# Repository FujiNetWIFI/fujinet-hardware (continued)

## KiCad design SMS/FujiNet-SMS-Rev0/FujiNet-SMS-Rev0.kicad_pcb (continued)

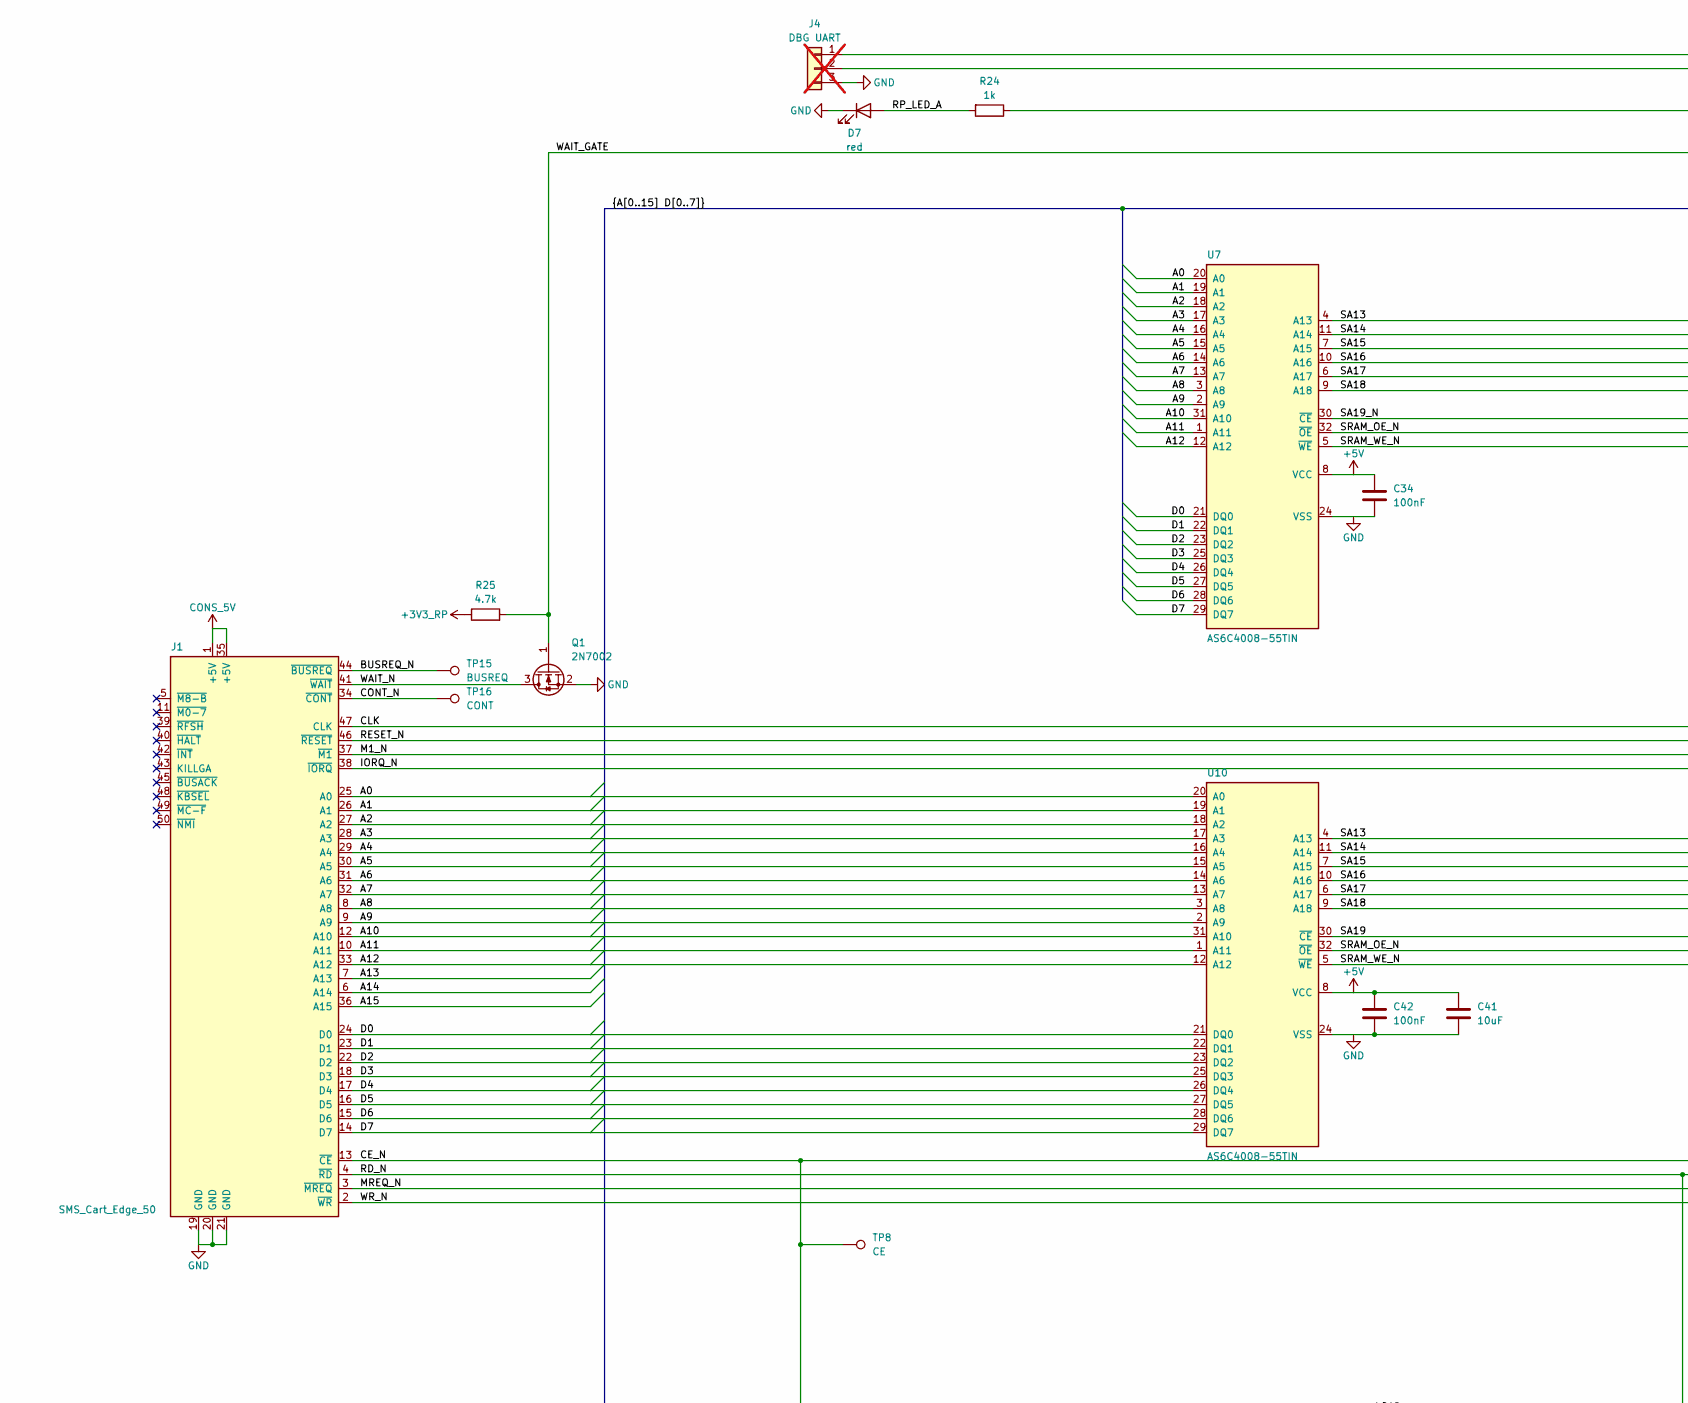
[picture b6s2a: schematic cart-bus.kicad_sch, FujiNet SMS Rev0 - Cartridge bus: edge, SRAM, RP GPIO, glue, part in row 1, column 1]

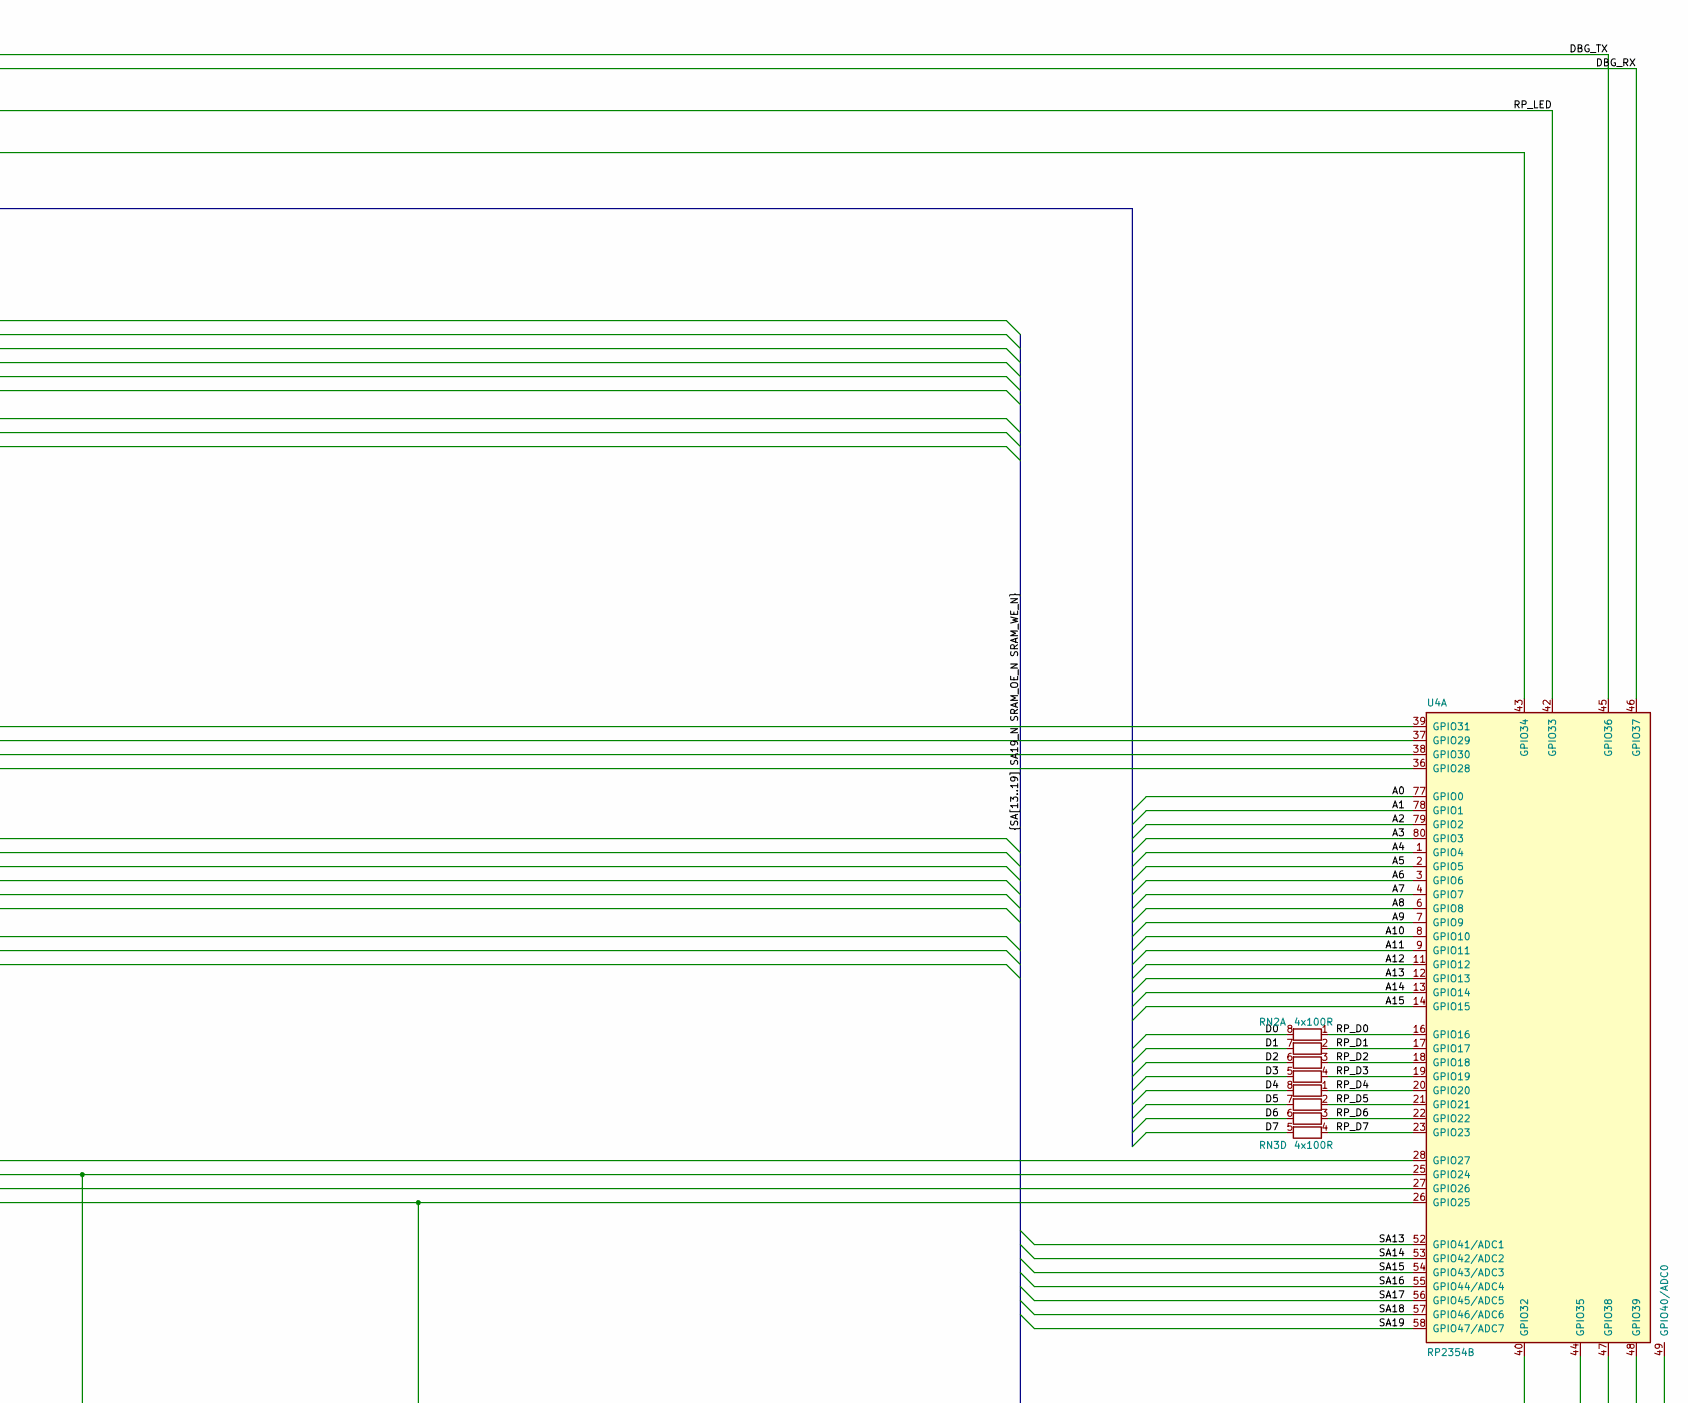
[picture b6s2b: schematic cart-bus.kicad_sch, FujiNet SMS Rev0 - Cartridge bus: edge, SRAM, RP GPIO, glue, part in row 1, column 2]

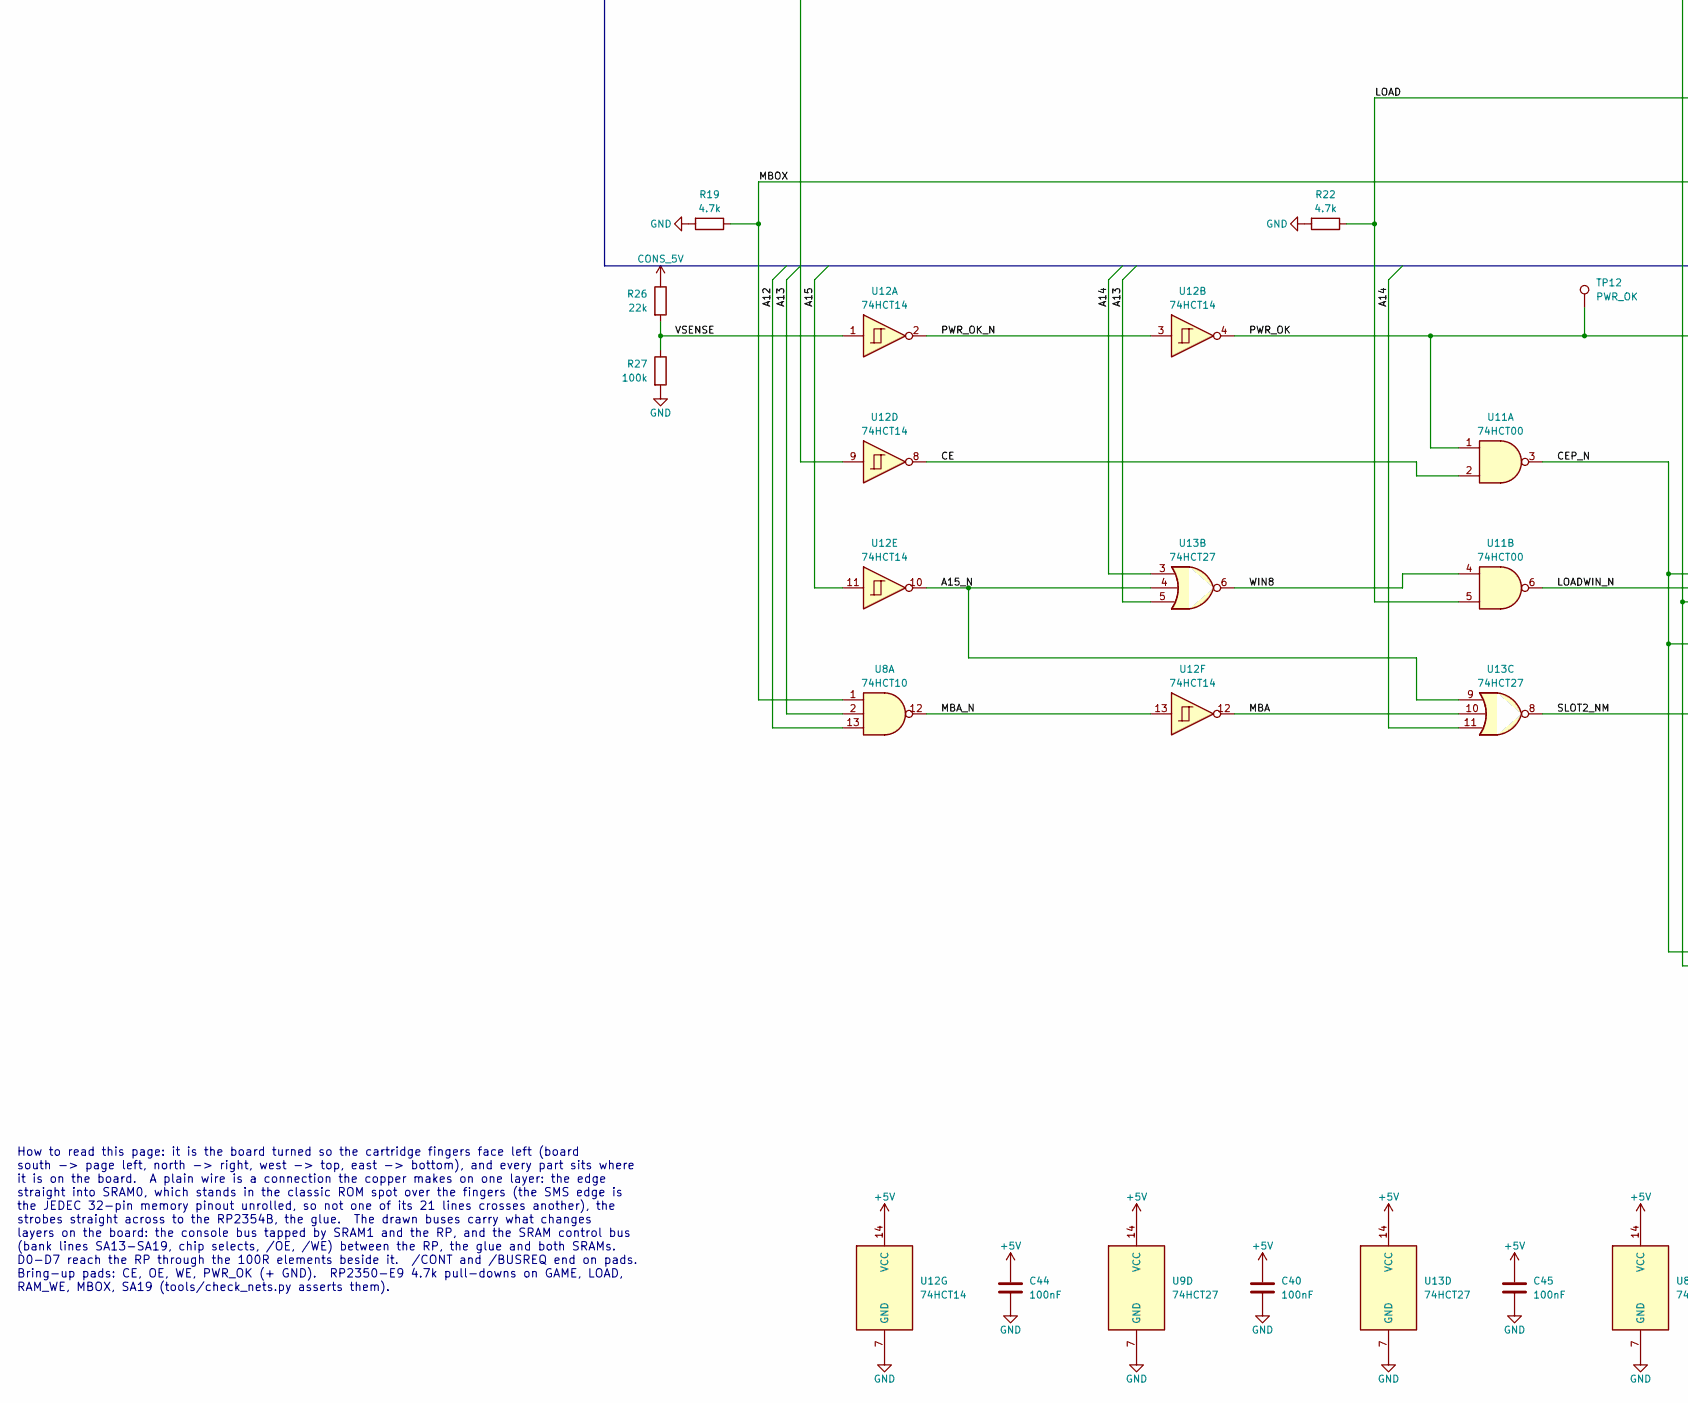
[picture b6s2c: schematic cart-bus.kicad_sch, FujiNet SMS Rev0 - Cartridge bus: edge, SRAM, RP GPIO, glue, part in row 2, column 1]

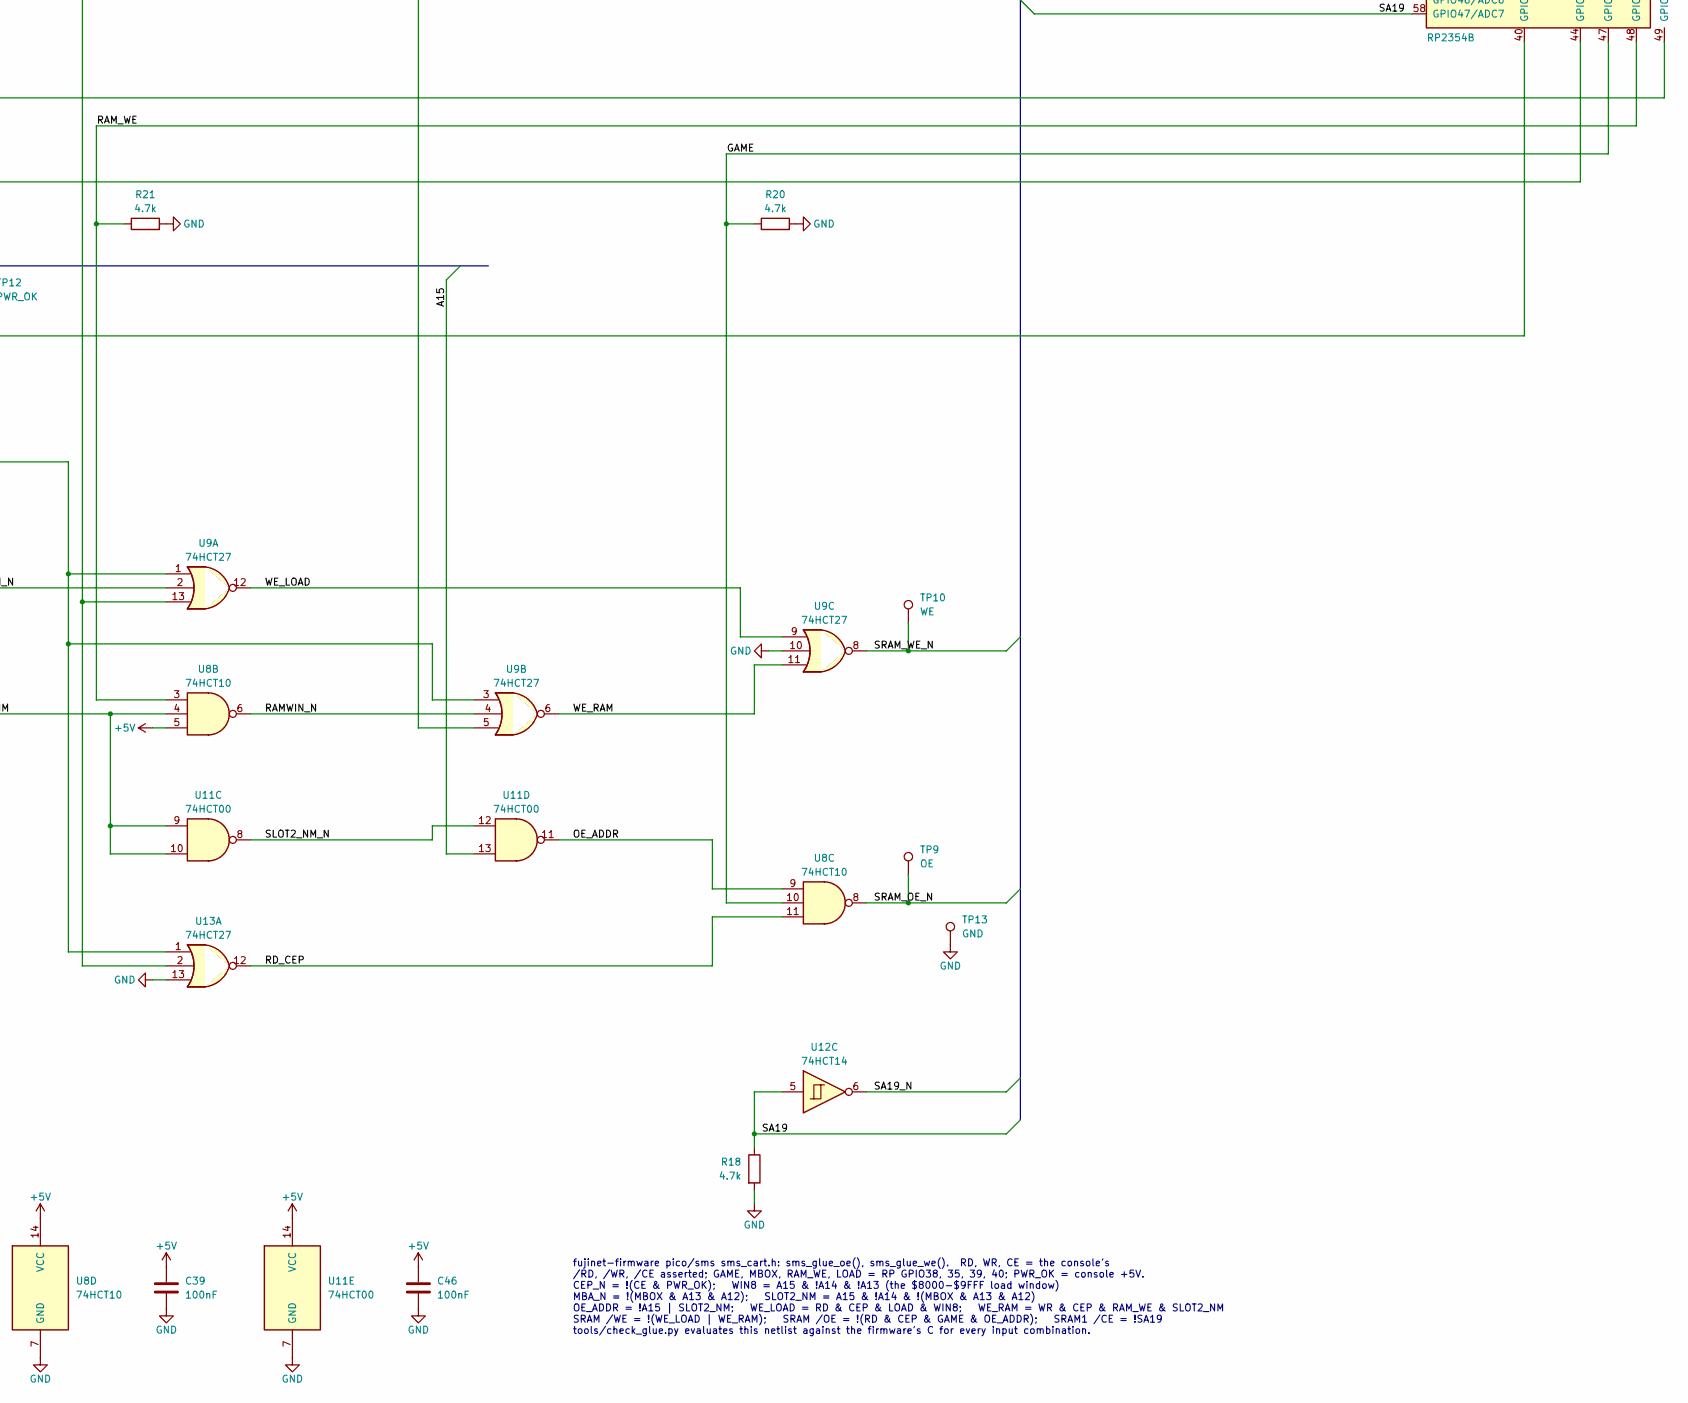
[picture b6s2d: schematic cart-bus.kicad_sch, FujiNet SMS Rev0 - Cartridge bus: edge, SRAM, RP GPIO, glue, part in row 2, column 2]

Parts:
C34, C39, C40, C42, C44, C45, C46: 100nF; C_0603_1608Metric; MPN CC0603KRX7R9BB104; LCSC C14663
C41: 10uF; C_0603_1608Metric; MPN CL10A106KP8NNNC; LCSC C19702
D7: red; LED_0603_1608Metric; MPN KT-0603R; LCSC C2286
J1: SMS_Cart_Edge_50
J4: DBG UART; PinHeader_1x03_P2.54mm_Vertical; MPN PZ254V-11-03P; LCSC C2937625; not fitted
Q1: 2N7002; SOT-23; MPN 2N7002; LCSC C8545
R18, R19, R20, R21, R22, R25: 4.7k; R_0603_1608Metric; MPN 0603WAF4701T5E; LCSC C23162
R24: 1k; R_0603_1608Metric; MPN 0603WAF1001T5E; LCSC C21190
R26: 22k; R_0603_1608Metric; MPN 0603WAF2202T5E; LCSC C31850
R27: 100k; R_0603_1608Metric; MPN 0603WAF1003T5E; LCSC C25803
RN2, RN3: 4x100R; R_Array_Convex_4x0603; MPN 4D03WGJ0101T5E; LCSC C25506
TP8: CE; TestPoint_Pad_D1.5mm
TP9: OE; TestPoint_Pad_D1.5mm
TP10: WE; TestPoint_Pad_D1.5mm
TP12: PWR_OK; TestPoint_Pad_D1.5mm
TP13: GND; TestPoint_Pad_D1.5mm
TP15: BUSREQ; TestPoint_Pad_D1.5mm
TP16: CONT; TestPoint_Pad_D1.5mm
U4: RP2354B; QFN-80-1EP_10x10mm_P0.4mm_EP3.4x3.4mm; MPN RP2354B; LCSC C39843328
U7, U10: AS6C4008-55TIN; TSOP-I-32_18.4x8mm_P0.5mm; MPN AS6C4008-55TIN; LCSC C5569980
U8: 74HCT10; SOIC-14_3.9x8.7mm_P1.27mm; MPN 74HCT10D,653; LCSC C547236
U9, U13: 74HCT27; SOIC-14_3.9x8.7mm_P1.27mm; MPN 74HCT27D,653; LCSC C5984
U11: 74HCT00; SOIC-14_3.9x8.7mm_P1.27mm; MPN SN74HCT00DR; LCSC C6764
U12: 74HCT14; SOIC-14_3.9x8.7mm_P1.27mm; MPN SN74HCT14DR; LCSC C6769

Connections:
+3V3_RP: R25.1; also elsewhere on the board
+5V: C34.1, C39.1, C40.1, C41.1, C42.1, C44.1, C45.1, C46.1, U7.8 (VCC), U8.5, U8.14 (VCC), U9.14 (VCC), U10.8 (VCC), U11.14 (VCC), U12.14 (VCC), U13.14 (VCC); also elsewhere on the board
/cart-bus/A0: J1.25 (A0), U4.77 (GPIO0), U7.20 (A0), U10.20 (A0)
/cart-bus/A1: J1.26 (A1), U4.78 (GPIO1), U7.19 (A1), U10.19 (A1)
/cart-bus/A2: J1.27 (A2), U4.79 (GPIO2), U7.18 (A2), U10.18 (A2)
/cart-bus/A3: J1.28 (A3), U4.80 (GPIO3), U7.17 (A3), U10.17 (A3)
/cart-bus/A4: J1.29 (A4), U4.1 (GPIO4), U7.16 (A4), U10.16 (A4)
/cart-bus/A5: J1.30 (A5), U4.2 (GPIO5), U7.15 (A5), U10.15 (A5)
/cart-bus/A6: J1.31 (A6), U4.3 (GPIO6), U7.14 (A6), U10.14 (A6)
/cart-bus/A7: J1.32 (A7), U4.4 (GPIO7), U7.13 (A7), U10.13 (A7)
/cart-bus/A8: J1.8 (A8), U4.6 (GPIO8), U7.3 (A8), U10.3 (A8)
/cart-bus/A9: J1.9 (A9), U4.7 (GPIO9), U7.2 (A9), U10.2 (A9)
/cart-bus/A10: J1.12 (A10), U4.8 (GPIO10), U7.31 (A10), U10.31 (A10)
/cart-bus/A11: J1.10 (A11), U4.9 (GPIO11), U7.1 (A11), U10.1 (A11)
/cart-bus/A12: J1.33 (A12), U4.11 (GPIO12), U7.12 (A12), U8.13, U10.12 (A12)
/cart-bus/A13: J1.7 (A13), U4.12 (GPIO13), U8.2, U13.5
/cart-bus/A14: J1.6 (A14), U4.13 (GPIO14), U13.3, U13.11
/cart-bus/A15: J1.36 (A15), U4.14 (GPIO15), U11.13, U12.11
/cart-bus/A15_N: U12.10, U13.4, U13.9
/cart-bus/BUSREQ_N: J1.44 (~BUSREQ), TP15.1
/cart-bus/CE: U11.2, U12.8
/cart-bus/CEP_N: U9.1, U9.3, U11.3, U13.1
/cart-bus/CE_N: J1.13 (~CE), TP8.1, U4.28 (GPIO27), U12.9
/cart-bus/CLK: J1.47 (CLK), U4.39 (GPIO31)
/cart-bus/CONT_N: J1.34 (~CONT), TP16.1
/cart-bus/D0: J1.24 (D0), RN2.8 (R1.2), U7.21 (DQ0), U10.21 (DQ0)
/cart-bus/D1: J1.23 (D1), RN2.7 (R2.2), U7.22 (DQ1), U10.22 (DQ1)
/cart-bus/D2: J1.22 (D2), RN2.6 (R3.2), U7.23 (DQ2), U10.23 (DQ2)
/cart-bus/D3: J1.18 (D3), RN2.5 (R4.2), U7.25 (DQ3), U10.25 (DQ3)
/cart-bus/D4: J1.17 (D4), RN3.8 (R1.2), U7.26 (DQ4), U10.26 (DQ4)
/cart-bus/D5: J1.16 (D5), RN3.7 (R2.2), U7.27 (DQ5), U10.27 (DQ5)
/cart-bus/D6: J1.15 (D6), RN3.6 (R3.2), U7.28 (DQ6), U10.28 (DQ6)
/cart-bus/D7: J1.14 (D7), RN3.5 (R4.2), U7.29 (DQ7), U10.29 (DQ7)
/cart-bus/DBG_RX: J4.2, U4.46 (GPIO37)
/cart-bus/DBG_TX: J4.1, U4.45 (GPIO36)
/cart-bus/GAME: R20.1, U4.47 (GPIO38), U8.10
/cart-bus/IORQ_N: J1.38 (~IORQ), U4.36 (GPIO28)
/cart-bus/LOAD: R22.1, U4.49 (GPIO40/ADC0), U11.5
/cart-bus/LOADWIN_N: U9.2, U11.6
/cart-bus/M1_N: J1.37 (~M1), U4.38 (GPIO30)
/cart-bus/MBA: U12.12, U13.10
/cart-bus/MBA_N: U8.12, U12.13
/cart-bus/MBOX: R19.1, U4.44 (GPIO35), U8.1
/cart-bus/MREQ_N: J1.3 (~MREQ), U4.27 (GPIO26)
/cart-bus/OE_ADDR: U8.9, U11.11
/cart-bus/PWR_OK: TP12.1, U4.40 (GPIO32), U11.1, U12.4
/cart-bus/PWR_OK_N: U12.2, U12.3
/cart-bus/RAMWIN_N: U8.6, U9.4
/cart-bus/RAM_WE: R21.1, U4.48 (GPIO39), U8.3
/cart-bus/RD_CEP: U8.11, U13.12
/cart-bus/RD_N: J1.4 (~RD), U4.25 (GPIO24), U9.13, U13.2
/cart-bus/RESET_N: J1.46 (~RESET), U4.37 (GPIO29)
/cart-bus/RP_D0: RN2.1 (R1.1), U4.16 (GPIO16)
/cart-bus/RP_D1: RN2.2 (R2.1), U4.17 (GPIO17)
/cart-bus/RP_D2: RN2.3 (R3.1), U4.18 (GPIO18)
/cart-bus/RP_D3: RN2.4 (R4.1), U4.19 (GPIO19)
/cart-bus/RP_D4: RN3.1 (R1.1), U4.20 (GPIO20)
/cart-bus/RP_D5: RN3.2 (R2.1), U4.21 (GPIO21)
/cart-bus/RP_D6: RN3.3 (R3.1), U4.22 (GPIO22)
/cart-bus/RP_D7: RN3.4 (R4.1), U4.23 (GPIO23)
/cart-bus/RP_LED: R24.1, U4.42 (GPIO33)
/cart-bus/RP_LED_A: D7.2 (A), R24.2
/cart-bus/SA13: U4.52 (GPIO41/ADC1), U7.4 (A13), U10.4 (A13)
/cart-bus/SA14: U4.53 (GPIO42/ADC2), U7.11 (A14), U10.11 (A14)
/cart-bus/SA15: U4.54 (GPIO43/ADC3), U7.7 (A15), U10.7 (A15)
/cart-bus/SA16: U4.55 (GPIO44/ADC4), U7.10 (A16), U10.10 (A16)
/cart-bus/SA17: U4.56 (GPIO45/ADC5), U7.6 (A17), U10.6 (A17)
/cart-bus/SA18: U4.57 (GPIO46/ADC6), U7.9 (A18), U10.9 (A18)
/cart-bus/SA19: R18.1, U4.58 (GPIO47/ADC7), U10.30 (~CE), U12.5
/cart-bus/SA19_N: U7.30 (~CE), U12.6
/cart-bus/SLOT2_NM: U8.4, U11.9, U11.10, U13.8
/cart-bus/SLOT2_NM_N: U11.8, U11.12
/cart-bus/SRAM_OE_N: TP9.1, U7.32 (~OE), U8.8, U10.32 (~OE)
/cart-bus/SRAM_WE_N: TP10.1, U7.5 (~WE), U9.8, U10.5 (~WE)
/cart-bus/VSENSE: R26.2, R27.1, U12.1
/cart-bus/WAIT_GATE: Q1.1 (G), R25.2, U4.43 (GPIO34)
/cart-bus/WAIT_N: J1.41 (~WAIT), Q1.3 (D)
/cart-bus/WE_LOAD: U9.9, U9.12
/cart-bus/WE_RAM: U9.6, U9.11
/cart-bus/WIN8: U11.4, U13.6
/cart-bus/WR_N: J1.2 (~WR), U4.26 (GPIO25), U9.5
CONS_5V: J1.1 (+5V), J1.35 (+5V), R26.1; also elsewhere on the board
GND: C34.2, C39.2, C40.2, C41.2, C42.2, C44.2, C45.2, C46.2, D7.1 (K), J1.19 (GND), J1.20 (GND), J1.21 (GND), J4.3, Q1.2 (S), R18.2, R19.2, R20.2, R21.2, R22.2, R27.2, TP13.1, U7.24 (VSS), U8.7 (GND), U9.7 (GND), U9.10, U10.24 (VSS), U11.7 (GND), U12.7 (GND), U13.7 (GND), U13.13; also elsewhere on the board

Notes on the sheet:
fujinet-firmware pico/sms sms_cart.h: sms_glue_oe(), sms_glue_we(). RD, WR, CE = the console's /RD, /WR, /CE asserted; GAME, MBOX, RAM_WE, LOAD = RP GPIO38, 35, 39, 40; PWR_OK = console +5V. CEP_N = !(CE & PWR_OK); WIN8 = A15 & !A14 & !A13 (the $8000-$9FFF load window) MBA_N = !(MBOX & A13 & A12); 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
How to read this page: it is the board turned so the cartridge fingers face left (board south -> page left, north -> right, west -> top, east -> bottom), and every part sits where it is on the board. A plain wire is a connection the copper makes on one layer: the edge straight into SRAM0, which sta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

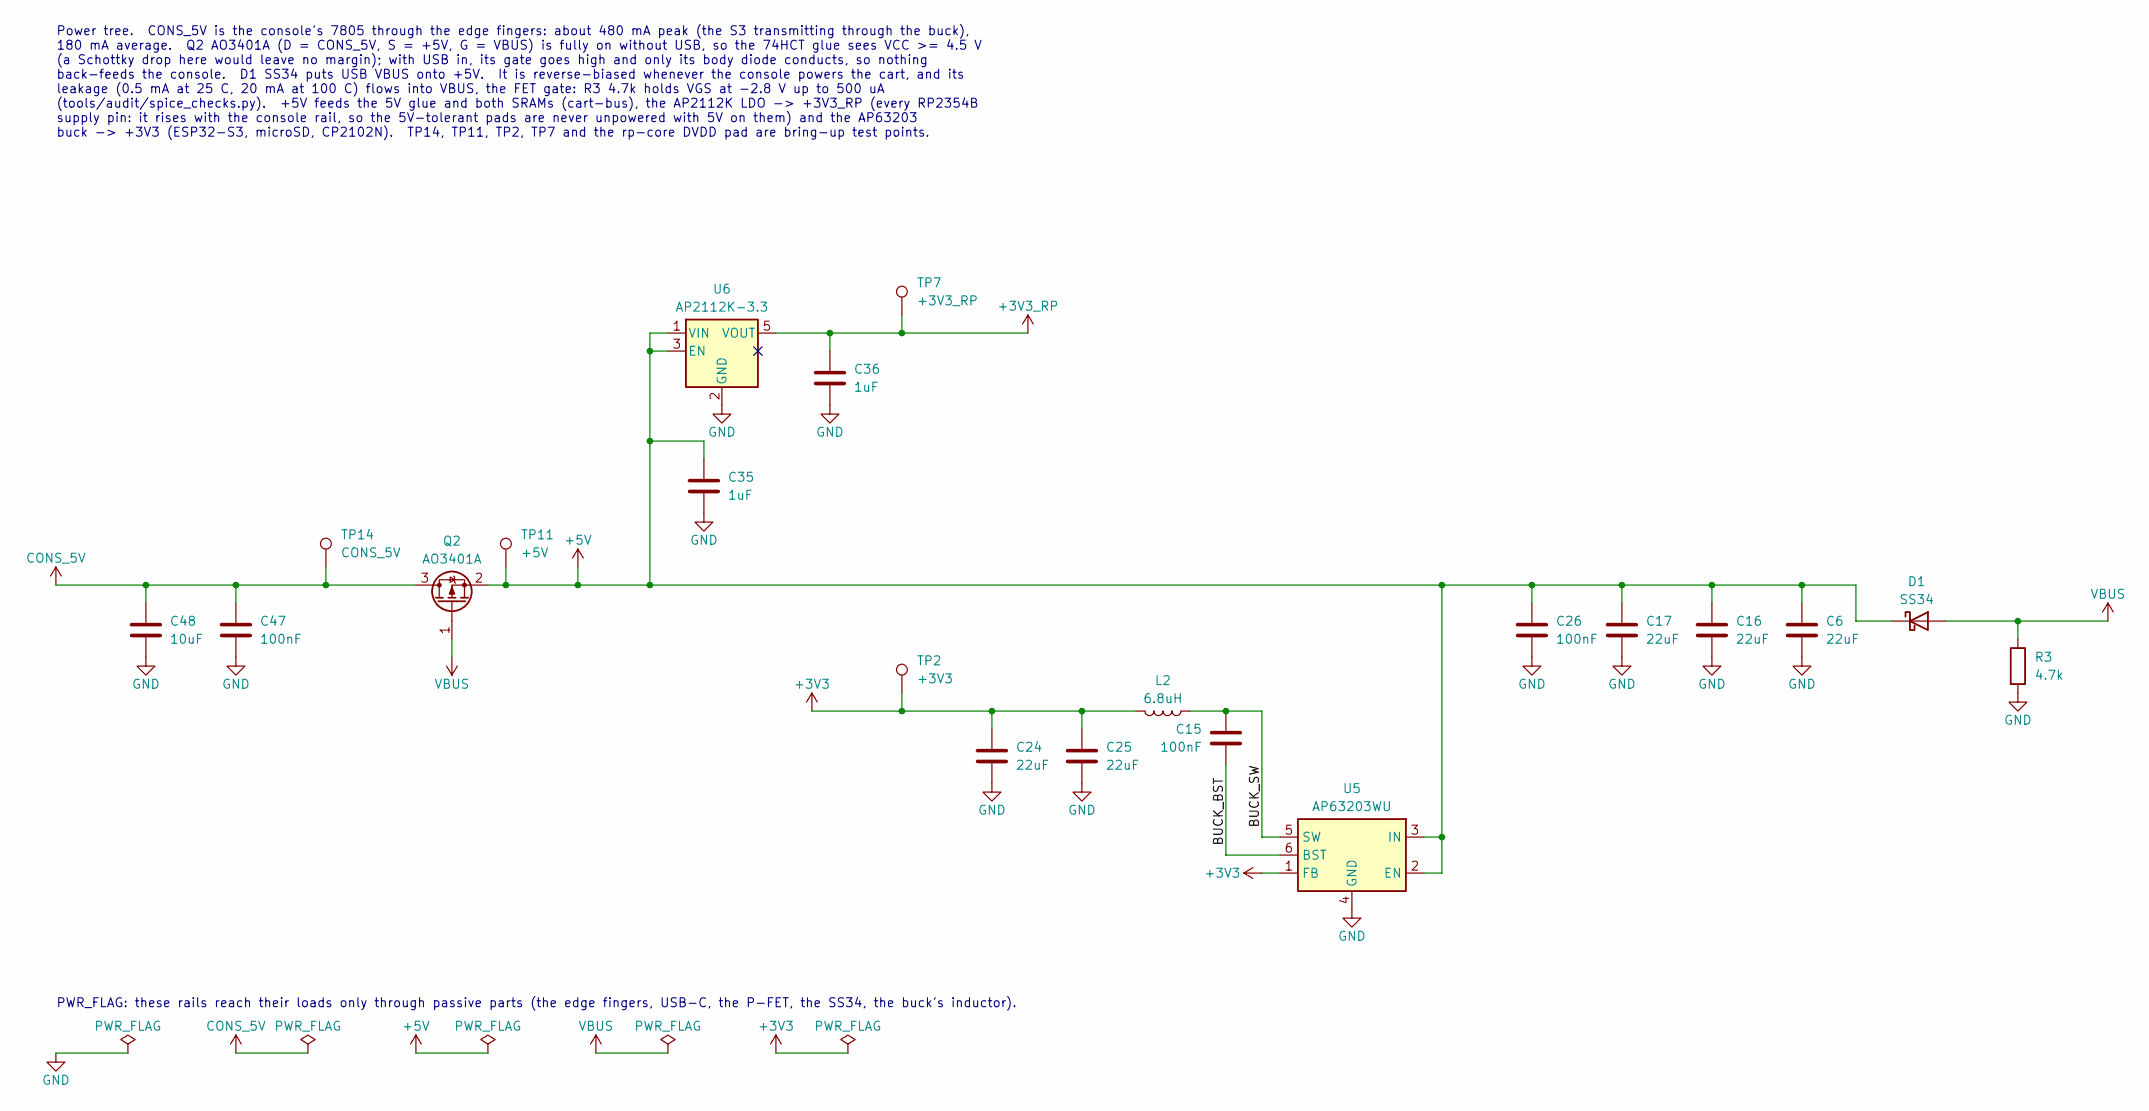
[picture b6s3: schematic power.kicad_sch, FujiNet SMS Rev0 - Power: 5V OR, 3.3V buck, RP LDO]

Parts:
C6, C16, C17, C24, C25: 22uF; C_0805_2012Metric; MPN CL21A226MAQNNNE; LCSC C45783
C15, C26, C47: 100nF; C_0603_1608Metric; MPN CC0603KRX7R9BB104; LCSC C14663
C35, C36: 1uF; C_0603_1608Metric; MPN CL10A105KB8NNNC; LCSC C15849
C48: 10uF; C_0603_1608Metric; MPN CL10A106KP8NNNC; LCSC C19702
D1: SS34; D_SMA; MPN SS34; LCSC C8678
L2: 6.8uH; L_Sunlord_SWPA4030S; MPN SWPA4030S6R8MT; LCSC C62684
Q2: AO3401A; SOT-23; MPN AO3401A; LCSC C15127
R3: 4.7k; R_0603_1608Metric; MPN 0603WAF4701T5E; LCSC C23162
TP2: +3V3; TestPoint_Pad_D1.5mm
TP7: +3V3_RP; TestPoint_Pad_D1.5mm
TP11: +5V; TestPoint_Pad_D1.5mm
TP14: CONS_5V; TestPoint_Pad_D1.5mm
U5: AP63203WU; TSOT-23-6; MPN AP63203WU-7; LCSC C780769
U6: AP2112K-3.3; SOT-23-5; MPN AP2112K-3.3TRG1; LCSC C51118

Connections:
+3V3: C24.1, C25.1, L2.2, TP2.1, U5.1 (FB); also elsewhere on the board
+3V3_RP: C36.1, TP7.1, U6.5 (VOUT); also elsewhere on the board
+5V: C6.1, C16.1, C17.1, C26.1, C35.1, D1.1 (K), Q2.2 (S), TP11.1, U5.2 (EN), U5.3 (IN), U6.1 (VIN), U6.3 (EN); also elsewhere on the board
/power/BUCK_BST: C15.2, U5.6 (BST)
/power/BUCK_SW: C15.1, L2.1, U5.5 (SW)
CONS_5V: C47.1, C48.1, Q2.3 (D), TP14.1; also elsewhere on the board
GND: C6.2, C16.2, C17.2, C24.2, C25.2, C26.2, C35.2, C36.2, C47.2, C48.2, R3.2, U5.4 (GND), U6.2 (GND); also elsewhere on the board
VBUS: D1.2 (A), Q2.1 (G), R3.1; also elsewhere on the board

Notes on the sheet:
PWR_FLAG: these rails reach their loads only through passive parts (the edge fingers, USB-C, the P-FET, the SS34, the buck's inductor).
Power tree. CONS_5V is the console's 7805 through the edge fingers: about 480 mA peak (the S3 transmitting through the buck), 180 mA average. Q2 AO3401A (D = CONS_5V, S = +5V, G = VBUS) is fully on without USB, so the 74HCT glue sees VCC >= 4.5 V (a Schottky drop here would leave no margin); with U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

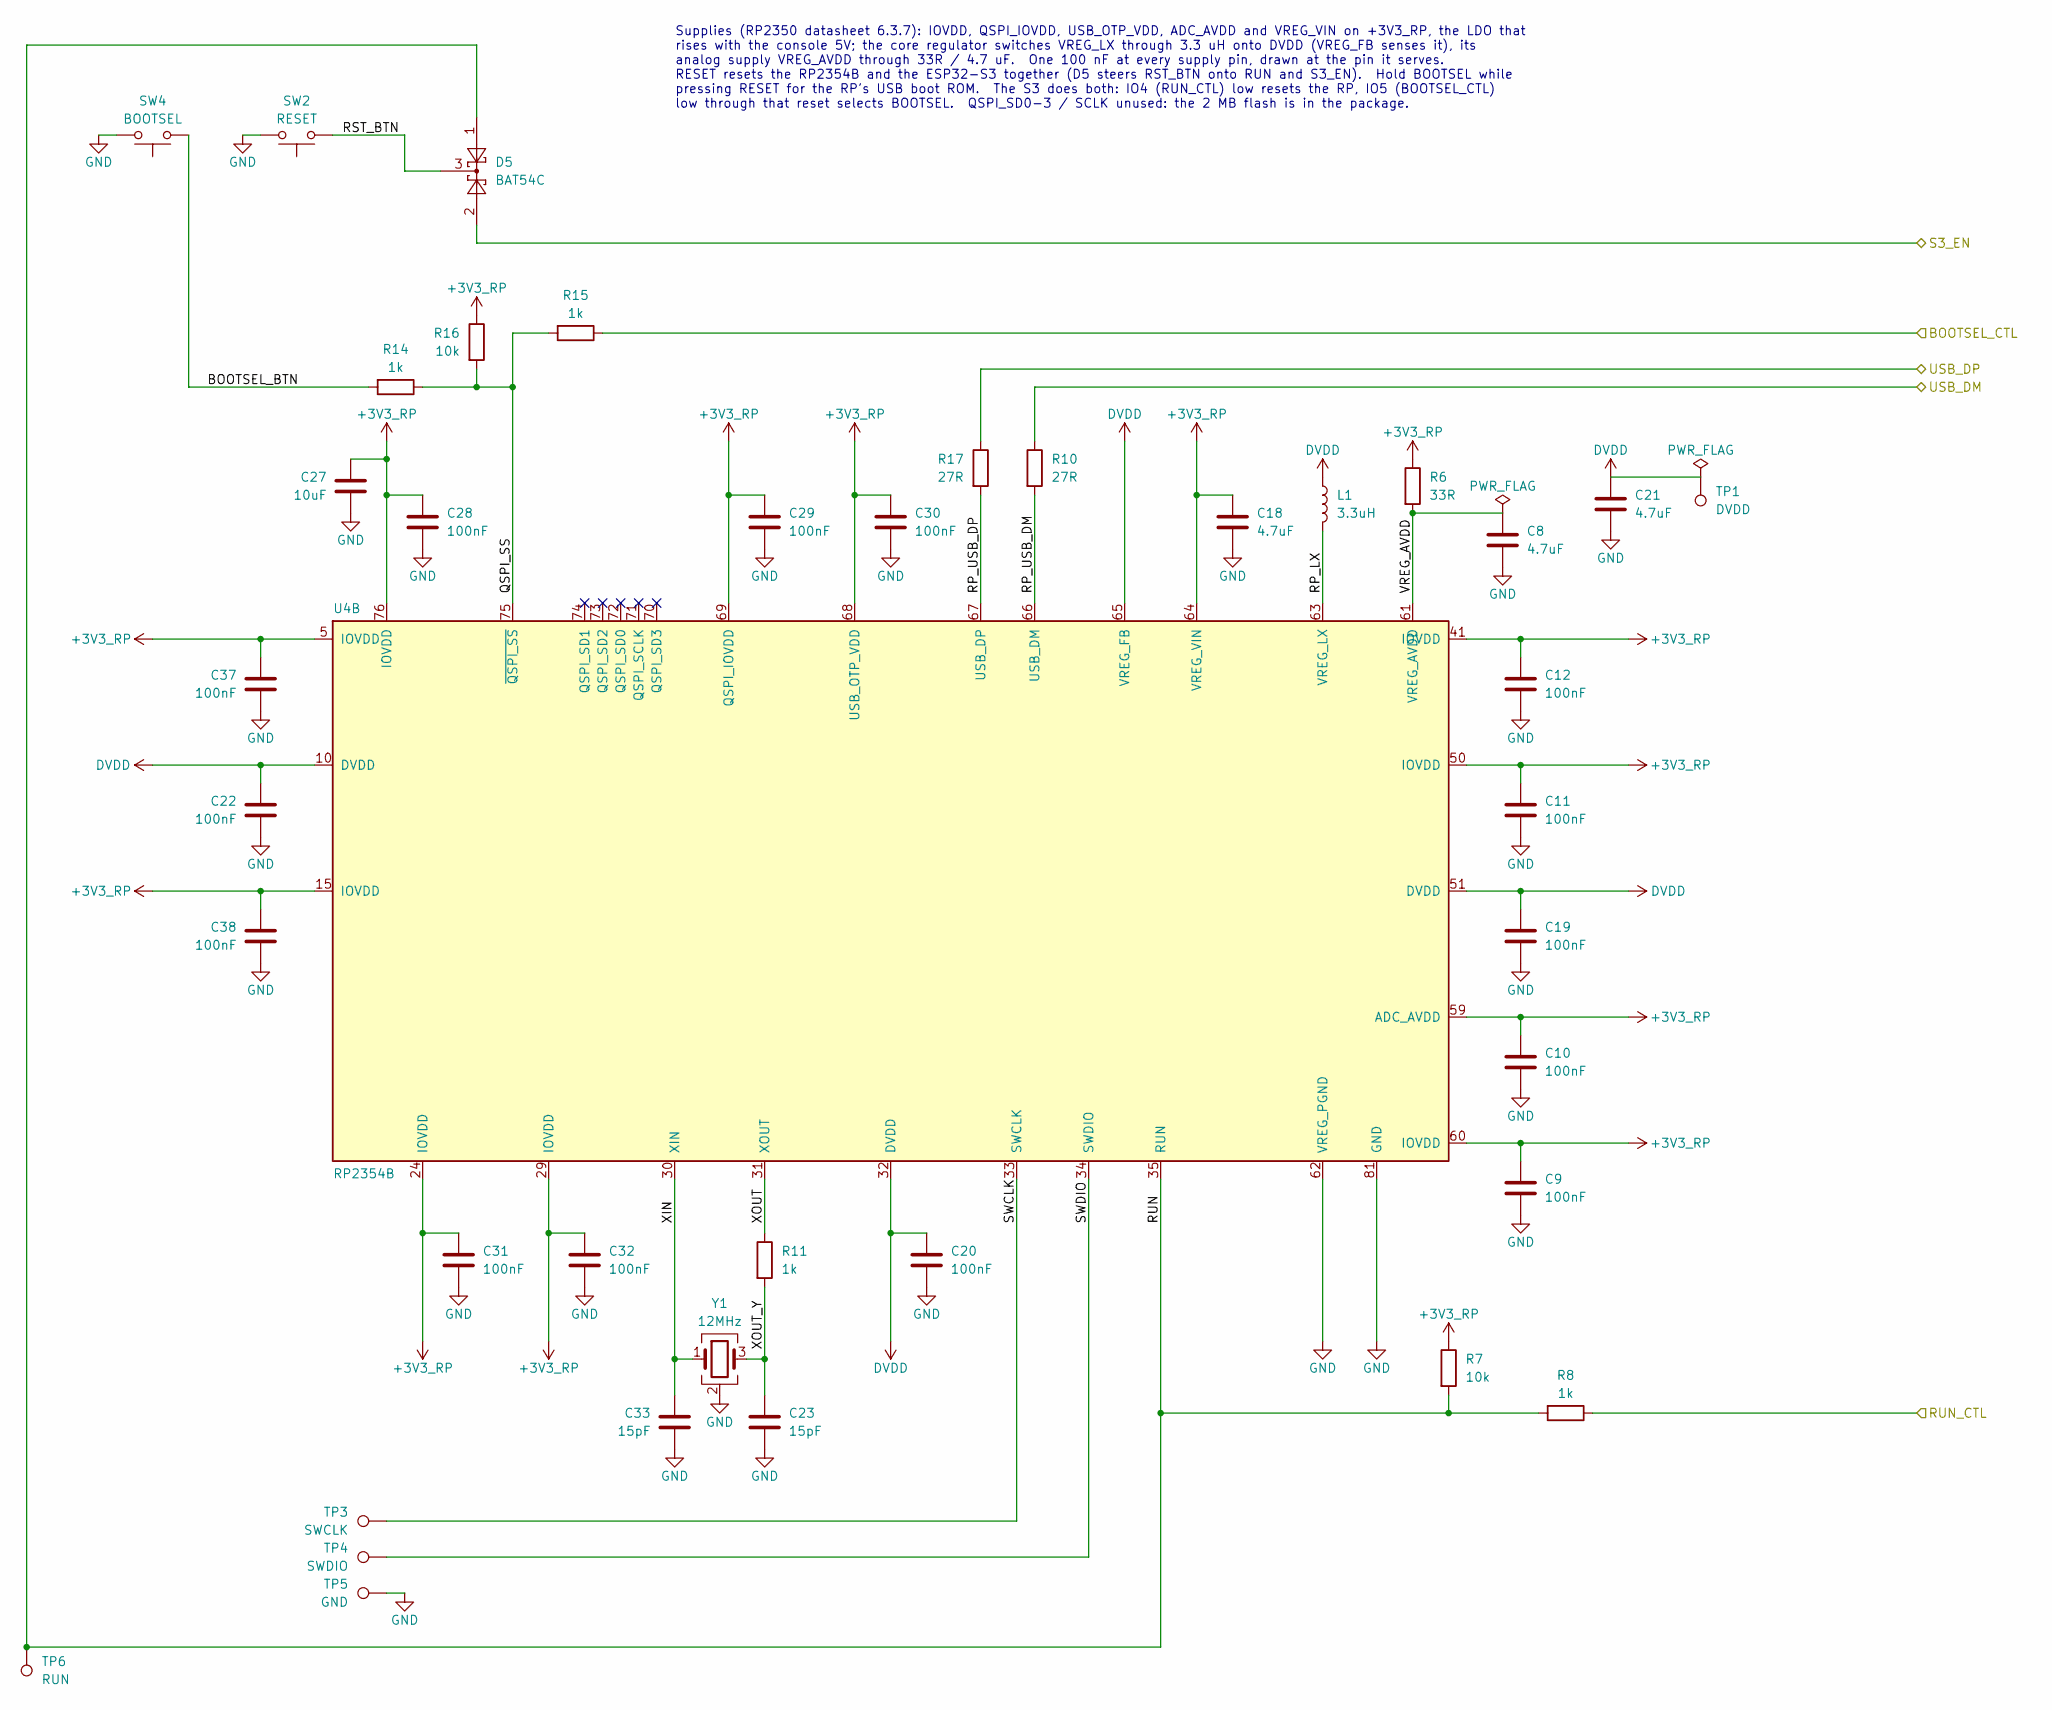
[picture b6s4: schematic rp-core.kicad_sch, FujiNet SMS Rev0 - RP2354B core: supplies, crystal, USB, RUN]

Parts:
C8, C18, C21: 4.7uF; C_0603_1608Metric; MPN CL10A475KO8NNNC; LCSC C19666
C9, C10, C11, C12, C19, C20, C22, C28, C29, C30, C31, C32, C37, C38: 100nF; C_0603_1608Metric; MPN CC0603KRX7R9BB104; LCSC C14663
C23, C33: 15pF; C_0603_1608Metric; MPN CL10C150JB8NNNC; LCSC C1644
C27: 10uF; C_0603_1608Metric; MPN CL10A106KP8NNNC; LCSC C19702
D5: BAT54C; SOT-23; MPN BAT54C,215; LCSC C37704
L1: 3.3uH; RPI_L_AOTA-B201610S3R3; MPN AOTA-B201610S3R3-101-T; LCSC C42411119
R6: 33R; R_0603_1608Metric; MPN 0603WAF330JT5E; LCSC C23140
R7, R16: 10k; R_0603_1608Metric; MPN 0603WAF1002T5E; LCSC C25804
R8, R11, R14, R15: 1k; R_0603_1608Metric; MPN 0603WAF1001T5E; LCSC C21190
R10, R17: 27R; R_0603_1608Metric; MPN 0603WAF270JT5E; LCSC C25190
SW2: RESET; SW_SPST_TS-1187A; MPN TS-1187A-B-A-B; LCSC C318884
SW4: BOOTSEL; SW_SPST_TS-1187A; MPN TS-1187A-B-A-B; LCSC C318884
TP1: DVDD; TestPoint_Pad_D1.5mm
TP3: SWCLK; TestPoint_Pad_D1.5mm
TP4: SWDIO; TestPoint_Pad_D1.5mm
TP5: GND; TestPoint_Pad_D1.5mm
TP6: RUN; TestPoint_Pad_D1.5mm
U4: RP2354B; QFN-80-1EP_10x10mm_P0.4mm_EP3.4x3.4mm; MPN RP2354B; LCSC C39843328
Y1: 12MHz; Crystal_SMD_3225-4Pin_3.2x2.5mm; MPN ABM8-272-T3; LCSC C20625731

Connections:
+3V3_RP: C9.1, C10.1, C11.1, C12.1, C18.1, C27.1, C28.1, C29.1, C30.1, C31.1, C32.1, C37.1, C38.1, R6.1, R7.1, R16.1, U4.5 (IOVDD), U4.15 (IOVDD), U4.24 (IOVDD), U4.29 (IOVDD), U4.41 (IOVDD), U4.50 (IOVDD), U4.59 (ADC_AVDD), U4.60 (IOVDD), U4.64 (VREG_VIN), U4.68 (USB_OTP_VDD), U4.69 (QSPI_IOVDD), U4.76 (IOVDD); also elsewhere on the board
/BOOTSEL_CTL: R15.1; also elsewhere on the board
/RUN_CTL: R8.1; also elsewhere on the board
/S3_EN: D5.2; also elsewhere on the board
/USB_DM: R10.1; also elsewhere on the board
/USB_DP: R17.1; also elsewhere on the board
/rp-core/BOOTSEL_BTN: R14.2, SW4.1
/rp-core/QSPI_SS: R14.1, R15.2, R16.2, U4.75 (~QSPI_SS)
/rp-core/RP_LX: L1.2, U4.63 (VREG_LX)
/rp-core/RP_USB_DM: R10.2, U4.66 (USB_DM)
/rp-core/RP_USB_DP: R17.2, U4.67 (USB_DP)
/rp-core/RST_BTN: D5.3, SW2.1
/rp-core/RUN: D5.1, R7.2, R8.2, TP6.1, U4.35 (RUN)
/rp-core/SWCLK: TP3.1, U4.33 (SWCLK)
/rp-core/SWDIO: TP4.1, U4.34 (SWDIO)
/rp-core/VREG_AVDD: C8.1, R6.2, U4.61 (VREG_AVDD)
/rp-core/XIN: C33.1, U4.30 (XIN), Y1.1
/rp-core/XOUT: R11.1, U4.31 (XOUT)
/rp-core/XOUT_Y: C23.1, R11.2, Y1.3
DVDD: C19.1, C20.1, C21.1, C22.1, L1.1, TP1.1, U4.10 (DVDD), U4.32 (DVDD), U4.51 (DVDD), U4.65 (VREG_FB)
GND: C8.2, C9.2, C10.2, C11.2, C12.2, C18.2, C19.2, C20.2, C21.2, C22.2, C23.2, C27.2, C28.2, C29.2, C30.2, C31.2, C32.2, C33.2, C37.2, C38.2, SW2.2, SW4.2, TP5.1, U4.62 (VREG_PGND), U4.81 (GND), Y1.2 (G), Y1.4 (G); also elsewhere on the board

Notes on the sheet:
Supplies (RP2350 datasheet 6.3.7): IOVDD, QSPI_IOVDD, USB_OTP_VDD, ADC_AVDD and VREG_VIN on +3V3_RP, the LDO that rises with the console 5V; the core regulator switches VREG_LX through 3.3 uH onto DVDD (VREG_FB senses it), its analog supply VREG_AVDD through 33R / 4.7 uF. One 100 nF at every supply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
